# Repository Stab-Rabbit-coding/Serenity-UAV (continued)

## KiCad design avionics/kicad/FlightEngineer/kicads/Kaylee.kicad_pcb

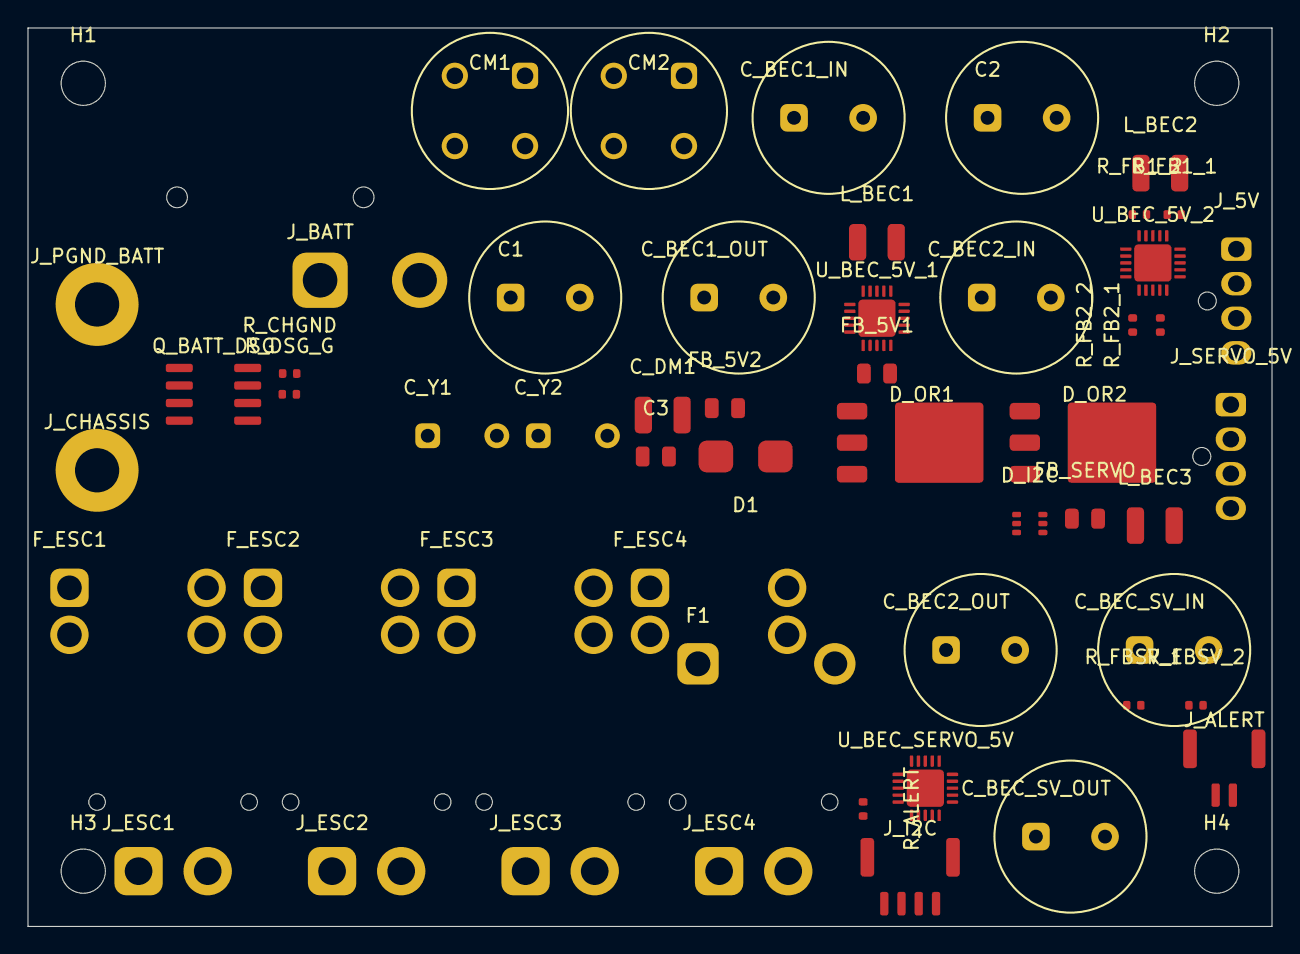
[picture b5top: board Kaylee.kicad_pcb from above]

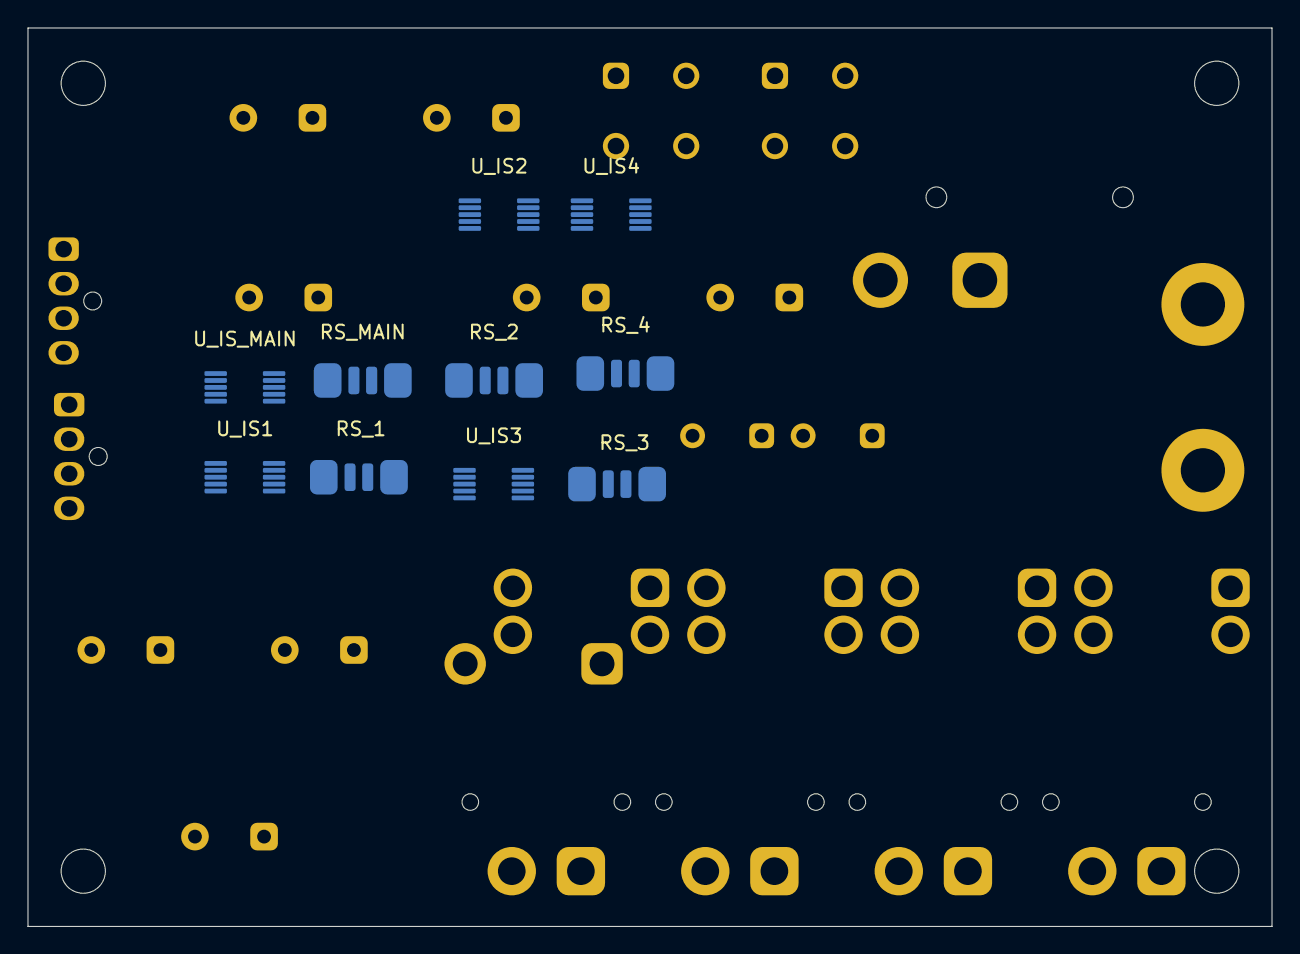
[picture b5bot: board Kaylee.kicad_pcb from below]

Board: 4 copper layers, 90.0 x 65.0 mm, 67 parts (10 on the bottom side), 39 nets, no tracks yet.

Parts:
C1, C2: 220uF/35V; CP_Radial_D10.0mm_P5.00mm
C3: 100nF/50V; C_0805_2012Metric
CM1, CM2: WE-SL5_7440640500; CMC_WE-SL5_7440640500
C_BEC1_IN, C_BEC1_OUT, C_BEC2_IN, C_BEC2_OUT: 100uF/50V; CP_Radial_D10.0mm_P5.00mm
C_BEC_SV_IN: 100uF/50V; CP_Radial_D10.0mm_P5.00mm
C_BEC_SV_OUT: 100uF/50V; CP_Radial_D10.0mm_P5.00mm
C_DM1: 10uF/50V; L_1210_3225Metric
C_Y1, C_Y2: 4.7nF/250V_Y2; C_Disc_D4.3mm_W1.9mm_P5.00mm
D1: SMBJ33CA; D_SMB
D_I2C: PRTR5V0U2X; SOT-363_SC-70-6
D_OR1, D_OR2: MBRD1045CT; TO-252-3_TabPin2
F1: FuseHolder_MAXI_150A; FuseHolder_MAXI_PCB
FB_5V1, FB_5V2: WE-742792612; C_0805_2012Metric
FB_SERVO: WE-742792612; C_0805_2012Metric
F_ESC1, F_ESC2, F_ESC3, F_ESC4: FuseHolder_Mini_40A; Fuseholder_Blade_Mini_Keystone_3568
H1, H2, H3, H4: M3; MountingHole_3.2mm_M3
J_5V: NanoFit-4P_5V; Molex_Nano-Fit_105309-xx04_1x04_P2.50mm_Vertical
J_ALERT: JST-GH_2P_ALERT; JST_GH_BM02B-GHS-TBT_1x02-1MP_P1.25mm_Vertical
J_BATT: XT60PW-F; AMASS_XT60PW-F_1x02_P7.20mm_Horizontal
J_CHASSIS: M3_Lug; MountingHole_3.2mm_M3_Pad_Via
J_ESC1: XT30PW-F_ESC1; AMASS_XT30PW-F_1x02_P2.50mm_Horizontal
J_ESC2: XT30PW-F_ESC2; AMASS_XT30PW-F_1x02_P2.50mm_Horizontal
J_ESC3: XT30PW-F_ESC3; AMASS_XT30PW-F_1x02_P2.50mm_Horizontal
J_ESC4: XT30PW-F_ESC4; AMASS_XT30PW-F_1x02_P2.50mm_Horizontal
J_I2C: JST-GH_4P_I2C; JST_GH_BM04B-GHS-TBT_1x04-1MP_P1.25mm_Vertical
J_PGND_BATT: M3_Lug; MountingHole_3.2mm_M3_Pad_Via
J_SERVO_5V: NanoFit-4P_6V; Molex_Nano-Fit_105309-xx04_1x04_P2.50mm_Vertical
L_BEC1, L_BEC2, L_BEC3: WE-744314100_10uH; L_1210_3225Metric
Q_BATT_DSG: AON6556; SOIC-8_3.9x4.9mm_P1.27mm
RS_1, RS_2, RS_3, RS_4: 1mOhm_Kelvin_2512; R_Shunt_CSS2H_2512K
RS_MAIN: 1mOhm_Kelvin_2512; R_Shunt_CSS2H_2512K
R_ALERT: 2.2k; R_0402_1005Metric
R_CHGND: 0R; R_0402_1005Metric
R_DSG_G: 10k; R_0402_1005Metric
R_FB1_1, R_FB2_1: 100k; R_0402_1005Metric
R_FB1_2, R_FB2_2: 22.1k; R_0402_1005Metric
R_FBSV_1: 100k; R_0402_1005Metric
R_FBSV_2: 30.1k; R_0402_1005Metric
U_BEC_5V_1, U_BEC_5V_2: TPS54620RGYT; Texas_RGP0020D_VQFN-20-1EP_4x4mm_P0.5mm_EP2.7x2.7mm
U_BEC_SERVO_5V: TPS54620 sync buck 5.0V servo rail (pkg verify); Texas_RGP0020D_VQFN-20-1EP_4x4mm_P0.5mm_EP2.7x2.7mm
U_IS1: INA226_0x40; MSOP-10_3x3mm_P0.5mm
U_IS2: INA226_0x41; MSOP-10_3x3mm_P0.5mm
U_IS3: INA226_0x42; MSOP-10_3x3mm_P0.5mm
U_IS4: INA226_0x43; MSOP-10_3x3mm_P0.5mm
U_IS_MAIN: INA226_0x44; MSOP-10_3x3mm_P0.5mm

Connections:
5V_SERVO: C_BEC_SV_OUT.1, J_SERVO_5V.3, J_SERVO_5V.4, L_BEC3.1, R_FBSV_1.1, U_BEC_SERVO_5V.11
+5V: D_I2C.6, D_OR1.2, D_OR2.2, J_5V.3, J_5V.4, J_I2C.2, R_ALERT.1, U_IS1.4, U_IS2.4, U_IS3.4, U_IS4.4, U_IS_MAIN.4
BEC1_FB: R_FB1_1.2, R_FB1_2.1
BEC1_PRE_OR: C_BEC1_OUT.1, D_OR1.1, L_BEC1.1, R_FB1_1.1, U_BEC_5V_1.11
BEC1_SW: L_BEC1.2, U_BEC_5V_1.5, U_BEC_5V_1.6
BEC1_VIN_F: C_BEC1_IN.1, FB_5V1.2, U_BEC_5V_1.1, U_BEC_5V_1.15, U_BEC_5V_1.16, U_BEC_5V_1.17, U_BEC_5V_1.18, U_BEC_5V_1.19, U_BEC_5V_1.20
BEC2_FB: R_FB2_1.2, R_FB2_2.1
BEC2_PRE_OR: C_BEC2_OUT.1, D_OR1.3, D_OR2.1, D_OR2.3, L_BEC2.1, R_FB2_1.1, U_BEC_5V_2.11
BEC2_SW: L_BEC2.2, U_BEC_5V_2.5, U_BEC_5V_2.6
BEC2_VIN_F: C_BEC2_IN.1, FB_5V2.2, U_BEC_5V_2.1, U_BEC_5V_2.15, U_BEC_5V_2.16, U_BEC_5V_2.17, U_BEC_5V_2.18, U_BEC_5V_2.19, U_BEC_5V_2.20
BECSV_FB: R_FBSV_1.2, R_FBSV_2.1
BECSV_SW: L_BEC3.2, U_BEC_SERVO_5V.5, U_BEC_SERVO_5V.6
BECSV_VIN_F: C_BEC_SV_IN.1, FB_SERVO.2, U_BEC_SERVO_5V.1, U_BEC_SERVO_5V.15, U_BEC_SERVO_5V.16, U_BEC_SERVO_5V.17, U_BEC_SERVO_5V.18, U_BEC_SERVO_5V.19, U_BEC_SERVO_5V.20
CHASSIS: C_Y1.2, C_Y2.2, R_CHGND.2
DSG_GATE: Q_BATT_DSG.8, R_DSG_G.1
ESC1_FUSED: F_ESC1.2, RS_1.1, U_IS1.10
ESC1_RS_OUT: J_ESC1.1, RS_1.4
ESC1_SNS_N: RS_1.3, U_IS1.2
ESC1_SNS_P: RS_1.2, U_IS1.1
ESC2_FUSED: F_ESC2.2, RS_2.1, U_IS2.10
ESC2_RS_OUT: J_ESC2.1, RS_2.4
ESC2_SNS_N: RS_2.3, U_IS2.2
ESC2_SNS_P: RS_2.2, U_IS2.1
ESC3_FUSED: F_ESC3.2, RS_3.1, U_IS3.10
ESC3_RS_OUT: J_ESC3.1, RS_3.4
ESC3_SNS_N: RS_3.3, U_IS3.2
ESC3_SNS_P: RS_3.2, U_IS3.1
ESC4_FUSED: F_ESC4.2, RS_4.1, U_IS4.10
ESC4_RS_OUT: J_ESC4.1, RS_4.4
ESC4_SNS_N: RS_4.3, U_IS4.2
ESC4_SNS_P: RS_4.2, U_IS4.1
MAIN_SNS_N: RS_MAIN.3, U_IS_MAIN.2
MAIN_SNS_P: RS_MAIN.2, U_IS_MAIN.1
PDB_ALERT_N: J_ALERT.2, R_ALERT.2, U_IS1.7, U_IS2.7, U_IS3.7, U_IS4.7, U_IS_MAIN.7
PDB_SCL: D_I2C.4, J_I2C.3, U_IS1.6, U_IS2.6, U_IS3.6, U_IS4.6, U_IS_MAIN.6
PDB_SDA: D_I2C.5, J_I2C.4, U_IS1.5, U_IS2.5, U_IS3.5, U_IS4.5, U_IS_MAIN.5
PGND: C1.2, C2.2, C3.2, CM1.3, CM1.4, CM2.3, CM2.4, C_BEC1_IN.2, C_BEC1_OUT.2, C_BEC2_IN.2, C_BEC2_OUT.2, C_BEC_SV_IN.2, C_BEC_SV_OUT.2, C_DM1.2, C_Y2.1, D1.1, D_I2C.1, J_5V.1, J_5V.2, J_ALERT.1, J_BATT.2, J_ESC1.2, J_ESC2.2, J_ESC3.2, J_ESC4.2, J_I2C.1, J_SERVO_5V.1, J_SERVO_5V.2, R_CHGND.1, R_DSG_G.2, R_FB1_2.2, R_FB2_2.2, R_FBSV_2.2, U_BEC_5V_1.7, U_BEC_5V_1.8, U_BEC_5V_1.9, U_BEC_5V_1.10, U_BEC_5V_1.21, U_BEC_5V_2.7, U_BEC_5V_2.8, U_BEC_5V_2.9, U_BEC_5V_2.10, U_BEC_5V_2.21, U_BEC_SERVO_5V.7, U_BEC_SERVO_5V.8, U_BEC_SERVO_5V.9, U_BEC_SERVO_5V.10, U_BEC_SERVO_5V.21, U_IS1.3, U_IS2.3, U_IS3.3, U_IS4.3, U_IS_MAIN.3
VBAT: F_ESC1.1, F_ESC2.1, F_ESC3.1, F_ESC4.1, Q_BATT_DSG.1, Q_BATT_DSG.2, Q_BATT_DSG.3, Q_BATT_DSG.4, RS_MAIN.1, RS_MAIN.4, U_IS_MAIN.10
VDIS: C1.1, C2.1, C3.1, CM1.1, CM1.2, CM2.1, CM2.2, C_DM1.1, C_Y1.1, D1.2, F1.1, F1.2, FB_5V1.1, FB_5V2.1, FB_SERVO.1, J_BATT.1, Q_BATT_DSG.5, Q_BATT_DSG.6, Q_BATT_DSG.7

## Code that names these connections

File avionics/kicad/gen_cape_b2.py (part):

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  C. Replacing MAX3485E (non-isolated RS-485) with ADM2795EBRWZ
     (isolated RS-485, SOIC-20W, ADI).
  D. Removing both DP83825I Ethernet PHY instances and all associated
     nets (RMII, MDC, MDIO, PHYx_*), replacing former connector pins
     with no_connect markers at PB2-P2.
  E. Keeping all other CAPE-B-1 components unchanged.
  F. Adding EMI-hardening passives:
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# ISOW1044BDFMR at (210, 170) — replaces ATA6561.
# Pin endpoint schematic coordinates when placed at (210, 170) with rot=0:
#   TXD  (pin 2) : x=197.30, y=170+(-1.27)=168.73   ← MCAN1_TX
#   STB_N(pin 3) : x=197.30, y=170+(+1.27)=171.27   ← CAN_STB
#   RXD  (pin 4) : x=197.30, y=170+(+3.81)=173.81   ← MCAN1_RX
#   VCC1 (pin 6) : x=197.30, y=170+(-5.08)=164.92
#   GND1 (pin 1) : x=197.30, y=170+(+6.35)=176.35
#   CANH (pin15) : x=222.70, y=170+(-2.54)=167.46   ← CAN_H
#   CANL (pin14) : x=222.70, y=170+(  0  )=170.00   ← CAN_L
#   VCC2 (pin11) : x=222.70, y=170+(-5.08)=164.92
#   ISOGND(pin10): x=222.70, y=170+(+2.54)=172.54
INST_ISOW1044 = """\
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
# ADM2795EBRWZ at (340, 170) — replaces MAX3485E.
# Pin endpoint schematic coordinates when placed at (340, 170) with rot=0:
#   DI   (pin 4) : x=327.30, y=170+(-2.54)=167.46   ← RS485_TX
#   DE   (pin 2) : x=327.30, y=170+(  0  )=170.00   ← RS485_DE
#   RE_N (pin 3) : x=327.30, y=170+(+2.54)=172.54   ← RS485_DE (tied)
#   RO   (pin 1) : x=327.30, y=170+(+5.08)=175.08   ← RS485_RX
#   VCC1 (pin 8) : x=327.30, y=170+(-5.08)=164.92
#   GND1 (pin 5) : x=327.30, y=170+(+7.62)=177.62
#   A    (pin19) : x=352.70, y=170+(-2.54)=167.46   ← RS485_A
#   B    (pin18) : x=352.70, y=170+(  0  )=170.00   ← RS485_B
#   VCC2 (pin16) : x=352.70, y=170+(-5.08)=164.92
#   GND2 (pin12) : x=352.70, y=170+(+2.54)=172.54
INST_ADM2795 = """\
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# 5. NO-CONNECT MARKERS for former PHY connector pins on PB2-P2
# ---------------------------------------------------------------------------
# PB2-P2 is at (65, 430).  Connector pin endpoints at x=67.54.
# RMII / MDC / MDIO / PHYx_* labels formerly connected at these y-values
# (from CAPE-B-1 line 1089–1198):
#   390.63, 393.17, 395.71, 398.25, 400.79, 403.33, 405.87, 408.41  (RMII0)
#   410.95, 413.49, 416.03, 418.57, 421.11, 423.65, 426.19, 428.73  (RMII1)
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    # Remove ETH2-PHY instance block (at 360, 455).
    text = remove_sexp_block(text, '  (symbol (lib_id "DP83825I") (at 360.00 455.00')

    # Remove global labels containing RMII, MDC, MDIO, PHY in their name.
    # These appear in two groups:
    #   (a) on PB2-P2 connector side (near y=390..444)
    #   (b) on PHY component side (near y=440..465 and 447..465)
    phy_label_patterns = [
        '  (global_label "RMII0_TXD0"',
        '  (global_label "RMII0_TXD1"',
        '  (global_label "RMII0_TX_EN"',
        '  (global_label "RMII0_RXD0"',
        '  (global_label "RMII0_RXD1"',
        '  (global_label "RMII0_CRS_DV"',
        '  (global_label "RMII0_RX_ER"',
        '  (global_label "RMII0_REF_CLK"',
        '  (global_label "RMII1_TXD0"',
        '  (global_label "RMII1_TXD1"',
        '  (global_label "RMII1_TX_EN"',
        '  (global_label "RMII1_RXD0"',
        '  (global_label "RMII1_RXD1"',
        '  (global_label "RMII1_CRS_DV"',
        '  (global_label "RMII1_RX_ER"',
        '  (global_label "RMII1_REF_CLK"',
        '  (global_label "MDC"',
        '  (global_label "MDIO"',
        '  (global_label "PHY1_INTRN"',
        '  (global_label "PHY1_RSTN"',
        '  (global_label "PHY2_INTRN"',
        '  (global_label "PHY2_RSTN"',
        '  (global_label "ETH1_TX_P"',
        '  (global_label "ETH1_TX_N"',
        '  (global_label "ETH1_RX_P"',
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
    # ------------------------------------------------------------------
    # F (instances). Insert all EMI components.
    # Replace the original CAN_H global label (output of ISOW1044 CANH)
    # with the wires + CMC + TVS chain, then re-insert the terminal labels.
    # ------------------------------------------------------------------

    # The original CAPE-B-1 had:
    #   (global_label "CAN_H" ... (at 222.70 167.46 0) ...)
    #   (global_label "CAN_L" ... (at 222.70 170.00 0) ...)
    # Replace them with wires routing to CMC_CAN.
    text = replace_sexp_block(
        text,
        '  (global_label "CAN_H" (shape bidirectional) (at 222.70 167.46 0)',
        WIRE_CANH_TO_CMC,
    )
    text = replace_sexp_block(
        text,
        '  (global_label "CAN_L" (shape bidirectional) (at 222.70 170.00 0)',
        WIRE_CANL_TO_CMC,
    )

    # Replace original RS485_A / RS485_B labels with routing wires.
    text = replace_sexp_block(
        text,
        '  (global_label "RS485_A" (shape bidirectional) (at 352.70 167.46 0)',
        WIRE_A_TO_CMC_RS485,
    )
    text = replace_sexp_block(
        text,
        '  (global_label "RS485_B" (shape bidirectional) (at 352.70 170.00 0)',
        WIRE_B_TO_CMC_RS485,
    )

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        else:
            print(f"OK   : '{token}' absent (correctly removed/replaced)")

    # RMII/MDC/MDIO labels should be gone.
    for token in ["RMII", '"MDC"', '"MDIO"']:
        n = dst_text.count(token)
        if n != 0:
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
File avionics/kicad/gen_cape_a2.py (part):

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  C. Replaces the MAX3485E RS-485 transceiver lib_symbol with ADM2795EBRWZ
     (isolated RS-485, SOIC-20W) and updates the corresponding symbol instance.
  D. Removes both DP83825I Ethernet PHY instances, their lib_symbol definition,
     all associated global_labels (RMII*, MDC, MDIO, PHY*_INTRN/RSTN, ETH*),
     associated power symbols and wires, and adds no_connect markers on the
     PB2-P2 connector pins that previously drove those signals.
  E. Adds new EMI protection components: SRF2012-100Y common-mode chokes,
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    VCC2 is connected to a 100 nF bypass cap (placed separately) on CAN_GND2.
    ISOGND connects to CAN_GND2 net label.
    CANH/CANL feed into the SRF2012 common-mode choke (CMC_CAN).
    TXD/STB_N/RXD connect to existing MCAN0_TX/CAN_STB/MCAN0_RX global labels.

    Args:
        cx: Component centre X coordinate (mm).
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    (pin "14" (uuid "{uid_p14}"))
    (pin "15" (uuid "{uid_p15}"))
  )
  (global_label "MCAN0_TX" (shape bidirectional) (at {left_x:.2f} {y_txd:.2f} 180)
    (effects (font (size 1.016 1.016)))
    (uuid "{next_uuid()}")
    (property "Intersheet References" "${{INTERSHEET_REFS}}" (at {left_x:.2f} {y_txd:.2f} 0)
      (effects (font (size 1.016 1.016)) (hide yes))))
  (global_label "CAN_STB" (shape bidirectional) (at {left_x:.2f} {y_stb_n:.2f} 180)
    (effects (font (size 1.016 1.016)))
    (uuid "{next_uuid()}")
    (property "Intersheet References" "${{INTERSHEET_REFS}}" (at {left_x:.2f} {y_stb_n:.2f} 0)
      (effects (font (size 1.016 1.016)) (hide yes))))
  (global_label "MCAN0_RX" (shape bidirectional) (at {left_x:.2f} {y_rxd:.2f} 180)
    (effects (font (size 1.016 1.016)))
    (uuid "{next_uuid()}")
    (property "Intersheet References" "${{INTERSHEET_REFS}}" (at {left_x:.2f} {y_rxd:.2f} 0)
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    (pin "17" (uuid "{uid_p17}"))
    (pin "20" (uuid "{uid_p20}"))
  )
  (global_label "RS485_TX" (shape bidirectional) (at {left_x:.2f} {y_di:.2f} 180)
    (effects (font (size 1.016 1.016)))
    (uuid "{next_uuid()}")
    (property "Intersheet References" "${{INTERSHEET_REFS}}" (at {left_x:.2f} {y_di:.2f} 0)
      (effects (font (size 1.016 1.016)) (hide yes))))
  (global_label "RS485_DE" (shape bidirectional) (at {left_x:.2f} {y_de:.2f} 180)
    (effects (font (size 1.016 1.016)))
    (uuid "{next_uuid()}")
    (property "Intersheet References" "${{INTERSHEET_REFS}}" (at {left_x:.2f} {y_de:.2f} 0)
      (effects (font (size 1.016 1.016)) (hide yes))))
  (wire (pts (xy {left_x:.2f} {y_ren:.2f}) (xy {left_x:.2f} {y_de:.2f}))
    (uuid "{next_uuid()}"))
  (global_label "RS485_RX" (shape bidirectional) (at {left_x:.2f} {y_ro:.2f} 180)
    (effects (font (size 1.016 1.016)))
    (uuid "{next_uuid()}")
    (property "Intersheet References" "${{INTERSHEET_REFS}}" (at {left_x:.2f} {y_ro:.2f} 0)
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    (uuid "{next_uuid()}")
    (property "Intersheet References" "${{INTERSHEET_REFS}}" (at {right_x:.2f} {y_gnd2:.2f} 0)
      (effects (font (size 1.016 1.016)) (hide yes))))
  (global_label "RS485_A" (shape bidirectional) (at {right_x:.2f} {y_a:.2f} 0)
    (effects (font (size 1.016 1.016)))
    (uuid "{next_uuid()}")
    (property "Intersheet References" "${{INTERSHEET_REFS}}" (at {right_x:.2f} {y_a:.2f} 0)
      (effects (font (size 1.016 1.016)) (hide yes))))
  (global_label "RS485_B" (shape bidirectional) (at {right_x:.2f} {y_b:.2f} 0)
    (effects (font (size 1.016 1.016)))
    (uuid "{next_uuid()}")
    (property "Intersheet References" "${{INTERSHEET_REFS}}" (at {right_x:.2f} {y_b:.2f} 0)
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
    CMC_CAN is placed at (335, 170) between the ISOW1044BDFMR CANH/CANL
    outputs and the external field connector net labels CAN_H_CMC / CAN_L_CMC.
    Pin L1A receives CAN_H from the transceiver; L1B drives CAN_H_CMC.
    Pin L2A receives CAN_L; L2B drives CAN_L_CMC.

    Args:
        cx: Component centre X (335).
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    except ValueError as exc:
        print(f"WARNING: ATA6561 instance not found: {exc}", file=sys.stderr)

    # Remove the old ATA6561 global_labels (MCAN0_TX / CAN_STB / MCAN0_RX
    # / CAN_H / CAN_L that were directly connected to ATA6561).
    # These are replaced by the labels inside inst_isow1044().
    # We identify them by their (at 297.30 ... 180) and (at 322.70 ... 0)
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        """Remove CAN labels at the ATA6561 instance position range."""
        # Pattern: global_label at y in [164, 175] connected to old chip.
        # We match on position strings (297.30 or 322.70) within y 164–176.
        for label_name in ("MCAN0_TX", "CAN_STB", "MCAN0_RX", "CAN_H", "CAN_L"):
            # Find all occurrences; remove those that sit in the ATA6561 area.
            pattern = re.compile(
                r'\n  \(global_label "' + re.escape(label_name) +
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    # (222.70, *) in the y=250–270 band (RS-485 area).
    def remove_rs485_max3485_labels(txt: str) -> str:
        """Remove RS-485 labels at the MAX3485E instance position range."""
        for label_name in ("RS485_TX", "RS485_DE", "RS485_RX", "RS485_A", "RS485_B"):
            pattern = re.compile(
                r'\n  \(global_label "' + re.escape(label_name) +
                r'" \(shape bidirectional\) \(at (?:197\.30|222\.70) 2[5-7]\d\.\d+ '
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
    text = remove_rs485_max3485_labels(text)

    # Also remove the second RS485_DE label at (197.30, 262.54) that
    # was tied to RE_N on MAX3485E (now handled by the wire in inst_adm2795).
    # The above loop handles both occurrences via repeated passes; do one
    # final targeted pass for the RE_N-tied one.
    text = re.sub(
        r'\n  \(global_label "RS485_DE" \(shape bidirectional\)'
        r' \(at 197\.30 262\.54 180\)[^\)]*\)[^\)]*\)',
        '',
        text,
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        except ValueError:
            break  # no more instances

    # Remove all global_labels whose names are PHY-specific (RMII*, MDC,
    # MDIO, PHY*_INTRN, PHY*_RSTN, ETH*_TX_*, ETH*_RX_*).
    # These labels appear both on PB2-P2 (left side) and near the PHY ICs.
    phy_label_pattern = re.compile(
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
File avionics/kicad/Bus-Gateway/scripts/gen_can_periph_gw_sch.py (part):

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    body.append(glabel("GND", 148.81 + off, 310, rot=0))
    body.append(sym_inst("C_Generic", f"C_ISO2{s}", "1uF", 145 + off, 316, footprint="Capacitor_SMD:C_0402_1005Metric"))
    body.append(glabel(f"ISO_5V_CAN{s}", 141.19 + off, 316, rot=180))
    body.append(glabel("ISO_GND_CAN", 148.81 + off, 316, rot=0))
    # NOTE: no PWR_FLAG needed on ISO_5V_CAN{s} -- pin 12 VISOOUT is itself a
    # real "power_out" pin (this chip's own internal isolated DC-DC output).
    # GND2/GISOIN (power_in / reference pins, not outputs) go straight onto
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    body.append(glabel("GND", 148.81 + off, 405, rot=0))
    body.append(sym_inst("C_Generic", f"C_RS2{s}", "100nF", 145 + off, 411, footprint="Capacitor_SMD:C_0402_1005Metric"))
    body.append(glabel(f"ISO_3V3_485{s}", 141.19 + off, 411, rot=180))
    body.append(glabel("ISO_GND_485", 148.81 + off, 411, rot=0))

    # -- J_ENC: AK7455 tilt-encoder input (ENC-NACELLE-1 pigtail-compatible) --
    body.append(
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            footprint="Serenity-Custom:Pigtail_7W_DirectSolder",
        )
    )
    enc_pins = ["GND", f"ENC_SPI_CS{s}", f"ENC_SPI_SCK{s}", f"ENC_SPI_MOSI{s}", f"ENC_SPI_MISO{s}", "+3V3", f"ENC_ERROR{s}"]
    for i, net in enumerate(enc_pins):
        body.append(glabel_conn(net, 60 + off, 500, 7, i))

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    body.append(glabel_pin_bynum("+5V", 25, 48, L, R, "1", SZ))
    body.append(glabel_pin_bynum("GND", 25, 48, L, R, "2", SZ))
    body.append(glabel_pin_bynum("+5V", 25, 48, L, R, "4", SZ))
    body.append(glabel_pin_bynum("U_REG_SW", 25, 48, L, R, "3", SZ))
    body.append(glabel_pin_bynum("U_REG_FB", 25, 48, L, R, "5", SZ))
    body.append(no_connect_pin_bynum(25, 48, L, R, "6", SZ))

    body.append(sym_inst("L_Generic", "L1", "2.2uH", 45, 45.46, footprint="Inductor_SMD:L_Taiyo-Yuden_NR-20xx"))
    body.append(glabel("U_REG_SW", 41.19, 45.46, rot=180))
    body.append(glabel("+3V3", 48.81, 45.46, rot=0))
    body.append(sym_inst("R_Generic", "R_FBT", "10k", 45, 54, footprint="Resistor_SMD:R_0402_1005Metric"))
    body.append(glabel("+3V3", 41.19, 54, rot=180))
    body.append(glabel("U_REG_FB", 48.81, 54, rot=0))
    body.append(sym_inst("R_Generic", "R_FBB", "20k", 45, 59, footprint="Resistor_SMD:R_0402_1005Metric"))
    body.append(glabel("U_REG_FB", 41.19, 59, rot=180))
    body.append(glabel("GND", 48.81, 59, rot=0))
    body.append(sym_inst("C_Generic", "C_IN", "10uF", 9, 48, footprint="Capacitor_SMD:C_0402_1005Metric"))
    body.append(glabel("+5V", 5.19, 48, rot=180))
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
    body.append(text_note("=== Shared CAN-FD bus: one physical multi-drop segment for every stack ===", bus_x, 280))
    body.append(sym_inst("Conn_JST_GH_03P", "J_CAN_IN", "CAN-FD trunk IN (CANH/CANL/GND)", bus_x, 300, footprint="Connector_JST:JST_GH_BM03B-GHS-TBT_1x03-1MP_P1.25mm_Vertical"))
    body.append(glabel_conn("CAN_H", bus_x, 300, 3, 0))
    body.append(glabel_conn("CAN_L", bus_x, 300, 3, 1))
    body.append(glabel_conn("ISO_GND_CAN", bus_x, 300, 3, 2))
    body.append(sym_inst("Conn_JST_GH_03P", "J_CAN_OUT", "CAN-FD trunk OUT (CANH/CANL/GND)", bus_x + 40, 300, footprint="Connector_JST:JST_GH_BM03B-GHS-TBT_1x03-1MP_P1.25mm_Vertical"))
    body.append(glabel_conn("CAN_H", bus_x + 40, 300, 3, 0))
    body.append(glabel_conn("CAN_L", bus_x + 40, 300, 3, 1))
    body.append(glabel_conn("ISO_GND_CAN", bus_x + 40, 300, 3, 2))
    body.append(sym_inst("R_Generic", "R_CANTERM", "120R", bus_x, 330, footprint="Resistor_SMD:R_0402_1005Metric"))
    body.append(glabel("CAN_H", bus_x - 3.81, 330, rot=180))
    body.append(glabel("CANTERM_MID", bus_x + 3.81, 330, rot=0))
    body.append(sym_inst("SJ_Generic", "SJ1", "open by default (VimDrones-style switchable 120R term)", bus_x + 20, 330, footprint="Jumper:SolderJumper-2_P1.3mm_Open_Pad1.0x1.5mm"))
    body.append(glabel("CANTERM_MID", bus_x + 16.19, 330, rot=180))
    body.append(glabel("CAN_L", bus_x + 23.81, 330, rot=0))
    body += pwr_flag("ISO_GND_CAN", bus_x + 60, 300)

    body.append(text_note("=== Shared RS-485 bus: one physical multi-drop segment for every stack ===", bus_x, 380))
    body.append(sym_inst("Conn_JST_GH_03P", "J_RS485_IN", "RS-485 trunk IN (A/B/GND)", bus_x, 400, footprint="Connector_JST:JST_GH_BM03B-GHS-TBT_1x03-1MP_P1.25mm_Vertical"))
    body.append(glabel_conn("RS485_A", bus_x, 400, 3, 0))
    body.append(glabel_conn("RS485_B", bus_x, 400, 3, 1))
    body.append(glabel_conn("ISO_GND_485", bus_x, 400, 3, 2))
    body.append(sym_inst("Conn_JST_GH_03P", "J_RS485_OUT", "RS-485 trunk OUT (A/B/GND)", bus_x + 40, 400, footprint="Connector_JST:JST_GH_BM03B-GHS-TBT_1x03-1MP_P1.25mm_Vertical"))
    body.append(glabel_conn("RS485_A", bus_x + 40, 400, 3, 0))
    body.append(glabel_conn("RS485_B", bus_x + 40, 400, 3, 1))
    body.append(glabel_conn("ISO_GND_485", bus_x + 40, 400, 3, 2))
    body.append(sym_inst("R_Generic", "R_485TERM", "120R", bus_x, 430, footprint="Resistor_SMD:R_0402_1005Metric"))
    body.append(glabel("RS485_A", bus_x - 3.81, 430, rot=180))
    body.append(glabel("TERM485_MID", bus_x + 3.81, 430, rot=0))
    body.append(sym_inst("SJ_Generic", "SJ2", "open by default", bus_x + 20, 430, footprint="Jumper:SolderJumper-2_P1.3mm_Open_Pad1.0x1.5mm"))
    body.append(glabel("TERM485_MID", bus_x + 16.19, 430, rot=180))
    body.append(glabel("RS485_B", bus_x + 23.81, 430, rot=0))
    body += pwr_flag("ISO_GND_485", bus_x + 60, 400)
    # No shared external isolated DC-DC needed -- each stack's own ISOW1412
    # (U4_i) has an integrated isolated DC-DC (see gen_stack()), same as
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
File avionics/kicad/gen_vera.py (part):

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        )
    )
    parts.append(glabel("GND", 20 - 3.81, 55, rot=180))
    parts.append(glabel("PGND", 20 + 3.81, 55, rot=0))
    parts.append(
        sym_inst(
            "C_Generic",
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        )
    )
    parts.append(glabel("GND", 20 - 3.81, 60, rot=180))
    parts.append(glabel("PGND", 20 + 3.81, 60, rot=0))

    cx, cy = 55, 40
    parts.append(sym_inst("TI_TPS65219", "U_PMIC", "TPS65219 PMIC", cx, cy))
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    parts.append(
        glabel_pin("RGMII1_RXD0", cx, cy, AM62A_L, AM62A_R, "RGMII1_RXD0", AM62A_SIZE)
    )
    parts.append(glabel_pin("MDIO", cx, cy, AM62A_L, AM62A_R, "MDIO", AM62A_SIZE))
    parts.append(glabel_pin("MDC", cx, cy, AM62A_L, AM62A_R, "MDC", AM62A_SIZE))
    # UART link to U3 (MSPM0G3507): crossed TX->RX, not net-name-matched TX->TX.
    parts.append(
        glabel_pin("UART_A2M", cx, cy, AM62A_L, AM62A_R, "MCU_UART_TX", AM62A_SIZE)
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    )

    parts.append(
        glabel_pin("TPM_SPI_CS", cx, cy, MSPM0_L, MSPM0_R, "SPI0_CS_TPM", MSPM0_SIZE)
    )
    parts.append(
        glabel_pin("TPM_SPI_SCK", cx, cy, MSPM0_L, MSPM0_R, "SPI0_SCK", MSPM0_SIZE)
    )
    parts.append(
        glabel_pin("TPM_SPI_MOSI", cx, cy, MSPM0_L, MSPM0_R, "SPI0_MOSI", MSPM0_SIZE)
    )
    parts.append(
        glabel_pin("TPM_SPI_MISO", cx, cy, MSPM0_L, MSPM0_R, "SPI0_MISO", MSPM0_SIZE)
    )
    parts.append(
        glabel_pin("TPM_PIRQ", cx, cy, MSPM0_L, MSPM0_R, "TPM_PIRQ", MSPM0_SIZE)
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        glabel_pin("SW_SPI_SCK", cx, cy, MSPM0_L, MSPM0_R, "SPI1_SCK", MSPM0_SIZE)
    )
    parts.append(
        glabel_pin("SW_SPI_MOSI", cx, cy, MSPM0_L, MSPM0_R, "SPI1_MOSI", MSPM0_SIZE)
    )
    parts.append(
        glabel_pin("SW_SPI_MISO", cx, cy, MSPM0_L, MSPM0_R, "SPI1_MISO", MSPM0_SIZE)
    )
    parts.append(
        glabel_pin("LASER_EN", cx, cy, MSPM0_L, MSPM0_R, "GPIO_LASER_EN", MSPM0_SIZE)
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        "J_ETH_OUT",
    )

    parts.append(glabel("PGND", 300, 240, rot=0))
    parts.append(glabel("PGND_SHIELD", 300, 243, rot=0))

    # =====================================================================
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    )
    parts.append(glabel_pin("CANFD_H", cx2, cy2, TVS_L, TVS_R, "A1", TVS_SIZE))
    parts.append(glabel_pin("CANFD_L", cx2, cy2, TVS_L, TVS_R, "A2", TVS_SIZE))
    parts.append(pwr_pin("PGND", cx2, cy2, TVS_L, TVS_R, "K", TVS_SIZE))

    # J_CANFD connector
    cx, cy = 100, 235
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
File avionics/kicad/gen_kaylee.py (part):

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

def lib_symbol_m3pad(name="M3_ChassisPad"):
    """Single-pin M3 chassis ground lug pad."""
    return f"""  (symbol "{name}" (in_bom yes) (on_board yes)
    (property "Reference" "TP" (at 0 -2.54 0) (effects (font (size 1.27 1.27))))
    (property "Value" "{name}" (at 0 2.54 0) (effects (font (size 1.27 1.27))))
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      (circle (center 0 0) (radius 1.0)
        (stroke (width 0.254) (type default)) (fill (type background))))
    (symbol "{name}_1_1"
{_pin_def("passive","line",-2.54,0,0,1.54,"PGND","1")})
  )"""


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    # -----------------------------------------------------------------------
    parts.append(text_note("=== Section A: Battery Input / Main Bus Filter ===", 10, 15))

    # J_BATT (XT60PW-F) — battery connector, pin1=+VBAT, pin2=PGND
    cx, cy = 20, 30
    parts.append(sym_inst("XT60PW_F", "J_BATT", "Amass XT60PW-F", cx, cy))
    parts.append(glabel("VBAT_IN_P", cx + 2.54, cy - 1.27, rot=0))
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    # C_Y1, C_Y2 — Y-class CM bypass caps
    parts.append(sym_inst("C_Generic", "C_Y1", "Kemet SA305E472MAR 4.7nF/250V Y2", 58, 48))
    parts.append(pwr_sym("VBAT",  58 - 2.54, 48, rot=0))
    parts.append(glabel("CHASSIS", 58 + 2.54, 48, rot=0))

    parts.append(sym_inst("C_Generic", "C_Y2", "Kemet SA305E472MAR 4.7nF/250V Y2", 65, 48))
    parts.append(pwr_sym("PGND",  65 - 2.54, 48, rot=0))
    parts.append(glabel("CHASSIS", 65 + 2.54, 48, rot=0))

    # -----------------------------------------------------------------------
    # Section B: Disconnect FET + main shunt + main INA226  (x=105..200, y=30)
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    # Q_BATT_DSG (AON6556): G=DSG_GATE, S=PGND, D=VBAT→VDIS
    cx, cy = 120, 30
    parts.append(sym_inst("AON6556", "Q_BATT_DSG", "AON6556 60V/30A NMOS", cx, cy))
    parts.append(glabel("DSG_GATE", cx - 7.62, cy - 2.54, rot=180))
    parts.append(pwr_sym("PGND",    cx - 7.62, cy + 2.54, rot=0))
    parts.append(pwr_sym("VBAT",    cx + 7.62, cy,         rot=180))

    # R_DSG_G — gate resistor 10k
    parts.append(sym_inst("R_Generic", "R_DSG_G", "10k 0402", cx - 12, cy + 10))
    parts.append(glabel("BQ_DSG_OUT", cx - 12 - 2.54, cy + 10, rot=180))
    parts.append(glabel("DSG_GATE",   cx - 12 + 2.54, cy + 10, rot=0))

    # R_CHGND — 0 Ohm chassis-PGND bond (socketed)
    parts.append(sym_inst("R_Generic", "R_CHGND", "0R 0402 (chassis-PGND bond, configurable)", cx - 12, cy + 18))
    parts.append(glabel("CHASSIS",    cx - 12 - 2.54, cy + 18, rot=180))
    parts.append(pwr_sym("PGND",      cx - 12 + 2.54, cy + 18, rot=180))

    # J_CHASSIS — M3 standoff pads (chassis bond point)
    parts.append(sym_inst("M3_ChassisPad", "J_CHASSIS", "M3 x8 brass standoff (x4)", cx - 5, cy + 25))
    parts.append(glabel("CHASSIS",    cx - 5 - 2.54, cy + 25, rot=180))

    # RS_MAIN — 1mΩ 4-terminal shunt (after Q_BATT_DSG drain, before VDIS)
    cx, cy = 150, 30
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    parts.append(pwr_sym("+5V",        cx - 10.16, cy + 2.54,  rot=0))   # VS
    # A0=GND (0x44: A0=GND, A1=VCC)
    parts.append(pwr_sym("PGND",       cx - 10.16, cy + 5.08,  rot=0))   # A0=GND
    parts.append(glabel("PDB_SDA",     cx + 10.16, cy - 5.08,  rot=0))   # SDA
    parts.append(glabel("PDB_SCL",     cx + 10.16, cy - 2.54,  rot=0))   # SCL
    parts.append(glabel("PDB_ALERT_N", cx + 10.16, cy,          rot=0))  # ALERT
    parts.append(pwr_sym("+5V",        cx + 10.16, cy + 2.54,  rot=180)) # A1=VCC (addr bit)
    parts.append(glabel("VDIS_SENSE",  cx + 10.16, cy + 5.08,  rot=0))  # VBUS

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            parts.append(pwr_sym(a0_net,       cx2 - 10.16, cy2 + 5.08,  rot=0))
        else:
            parts.append(glabel(a0_net,        cx2 - 10.16, cy2 + 5.08, rot=180))
        parts.append(glabel("PDB_SDA",         cx2 + 10.16, cy2 - 5.08, rot=0))
        parts.append(glabel("PDB_SCL",         cx2 + 10.16, cy2 - 2.54, rot=0))
        parts.append(glabel("PDB_ALERT_N",     cx2 + 10.16, cy2,         rot=0))
        # A1 pin
        if a1_net in ("PGND", "+5V"):
            parts.append(pwr_sym(a1_net,       cx2 + 10.16, cy2 + 2.54, rot=180))
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    # BAT+ (pack reference)
    parts.append(pwr_sym("VBAT",      ucx + 15.24, ucy - 15.24,  rot=180))
    # SDA/SCL
    parts.append(glabel("PDB_SDA",    ucx + 15.24, ucy - 12.70,  rot=0))
    parts.append(glabel("PDB_SCL",    ucx + 15.24, ucy - 10.16,  rot=0))
    # ALERT_N
    parts.append(glabel("PDB_ALERT_N", ucx + 15.24, ucy - 7.62,  rot=0))
    # DSG gate
    parts.append(glabel("BQ_DSG_OUT", ucx + 15.24, ucy - 5.08,   rot=0))
    # CHG gate — no-connect (DNP charge FET path)
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    parts.append(glabel("PDB_SCL_RAW", 555 - 7.62, 35 + 2.54, rot=180))
    parts.append(pwr_sym("+5V",        555 + 7.62, 35 - 2.54, rot=180))
    parts.append(nc(555 + 7.62, 35))                             # D2A — unused second diode anode
    parts.append(glabel("PDB_SDA",     555 + 7.62, 35 + 2.54, rot=0))

    # Short wire: PDB_SDA_RAW == PDB_SDA at this device boundary
    # (The TVS routes PDB_SDA through D_I2C; both labels used at ports)
    # Tie SCL through similarly
    parts.append(glabel("PDB_SCL_RAW", 548, 45, rot=180))
    parts.append(glabel("PDB_SCL",     552, 45, rot=0))

    # R_ALERT — 2.2kΩ pull-up for ALERT_N bus
    parts.append(sym_inst("R_Generic", "R_ALERT", "2.2k 0402 ALERT pull-up to +5V", 570, 50))
    parts.append(pwr_sym("+5V",         570 - 2.54, 50, rot=0))
    parts.append(glabel("PDB_ALERT_N",  570 + 2.54, 50, rot=0))

    # J_I2C — JST-GH 4-pin to Wash/Shepherd Bay A
    parts.append(sym_inst("Conn_JST_GH_04P", "J_I2C",
                          "JST-GH SM04B-GHS-TB 4P 1.25mm PDB I2C to FC1", 590, 38))
    parts.append(pwr_sym("PGND",        590 + 2.54, 38 - 3.81, rot=180))
    parts.append(pwr_sym("+5V",         590 + 2.54, 38 - 1.27, rot=0))
    parts.append(glabel("PDB_SCL",      590 + 2.54, 38 + 1.27, rot=0))
    parts.append(glabel("PDB_SDA",      590 + 2.54, 38 + 3.81, rot=0))

    parts.append(sym_inst("M3_ChassisPad", "J_SHLD_I2C", "PGND via-pad I2C cable shield", 590, 52))
    parts.append(pwr_sym("PGND", 590 - 2.54, 52, rot=0))
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    parts.append(sym_inst("Conn_JST_GH_02P", "J_ALERT",
                          "JST-GH SM02B-GHS-TB 2P 1.25mm ALERT to Wash GPIO", 590, 65))
    parts.append(pwr_sym("PGND",        590 + 2.54, 65 - 1.27, rot=180))
    parts.append(glabel("PDB_ALERT_N",  590 + 2.54, 65 + 1.27, rot=0))

    parts.append(sym_inst("M3_ChassisPad", "J_SHLD_ALERT", "PGND via-pad ALERT cable shield", 590, 75))
    parts.append(pwr_sym("PGND", 590 - 2.54, 75, rot=0))
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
